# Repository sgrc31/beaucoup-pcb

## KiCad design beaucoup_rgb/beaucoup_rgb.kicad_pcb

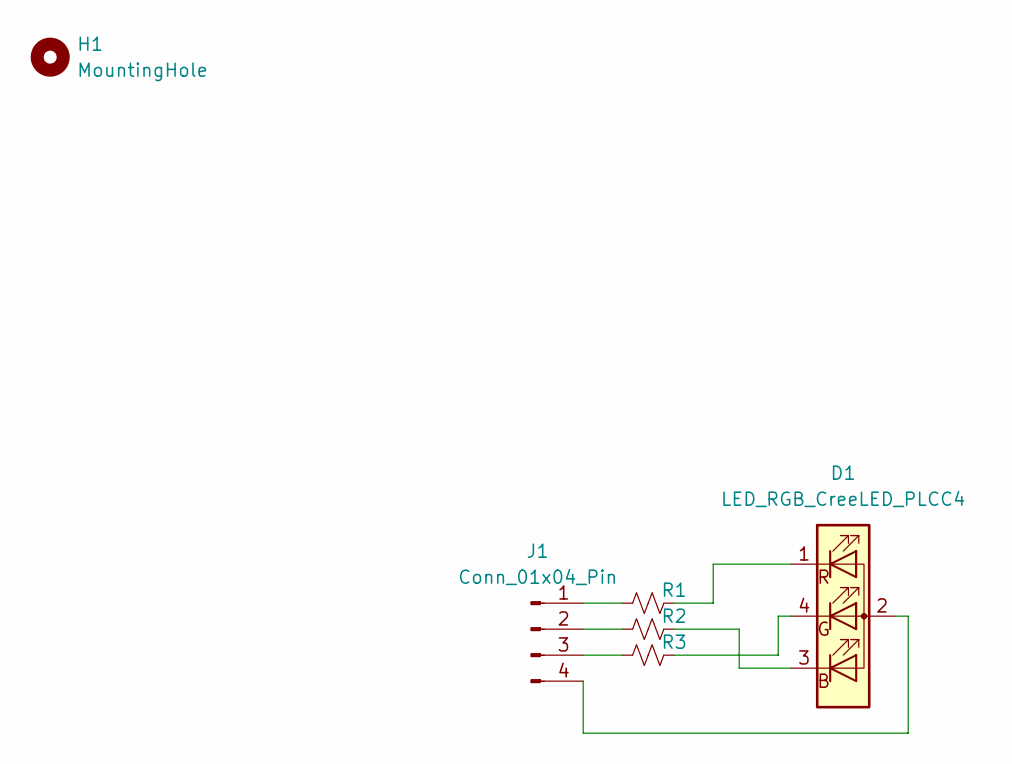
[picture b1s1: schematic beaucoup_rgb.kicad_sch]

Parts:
D1: LED_RGB_CreeLED_PLCC4; LED_RGB_CreeLED_CLV1A-FKB
H1: MountingHole; MountingHole_3.2mm_M3_ISO7380_Pad_TopOnly
J1: Conn_01x04_Pin; JST_XH_B4B-XH-A_1x04_P2.50mm_Vertical
R1, R2, R3: R_Small_US; R_1206_3216Metric_Pad1.30x1.75mm_HandSolder

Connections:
unnamed: D1.2 (A), J1.4
unnamed: D1.3 (BK), R2.1
unnamed: D1.4 (GK), R3.2
unnamed: D1.1 (RK), R1.2
unnamed: J1.1, R1.1
unnamed: J1.2, R2.2
unnamed: J1.3, R3.1

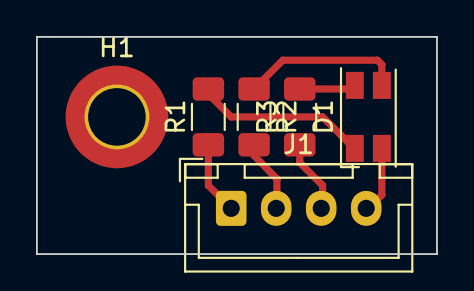
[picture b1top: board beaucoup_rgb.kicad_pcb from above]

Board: 2 copper layers, 22.2 x 12.1 mm, 6 parts (0 on the bottom side), 7 nets.

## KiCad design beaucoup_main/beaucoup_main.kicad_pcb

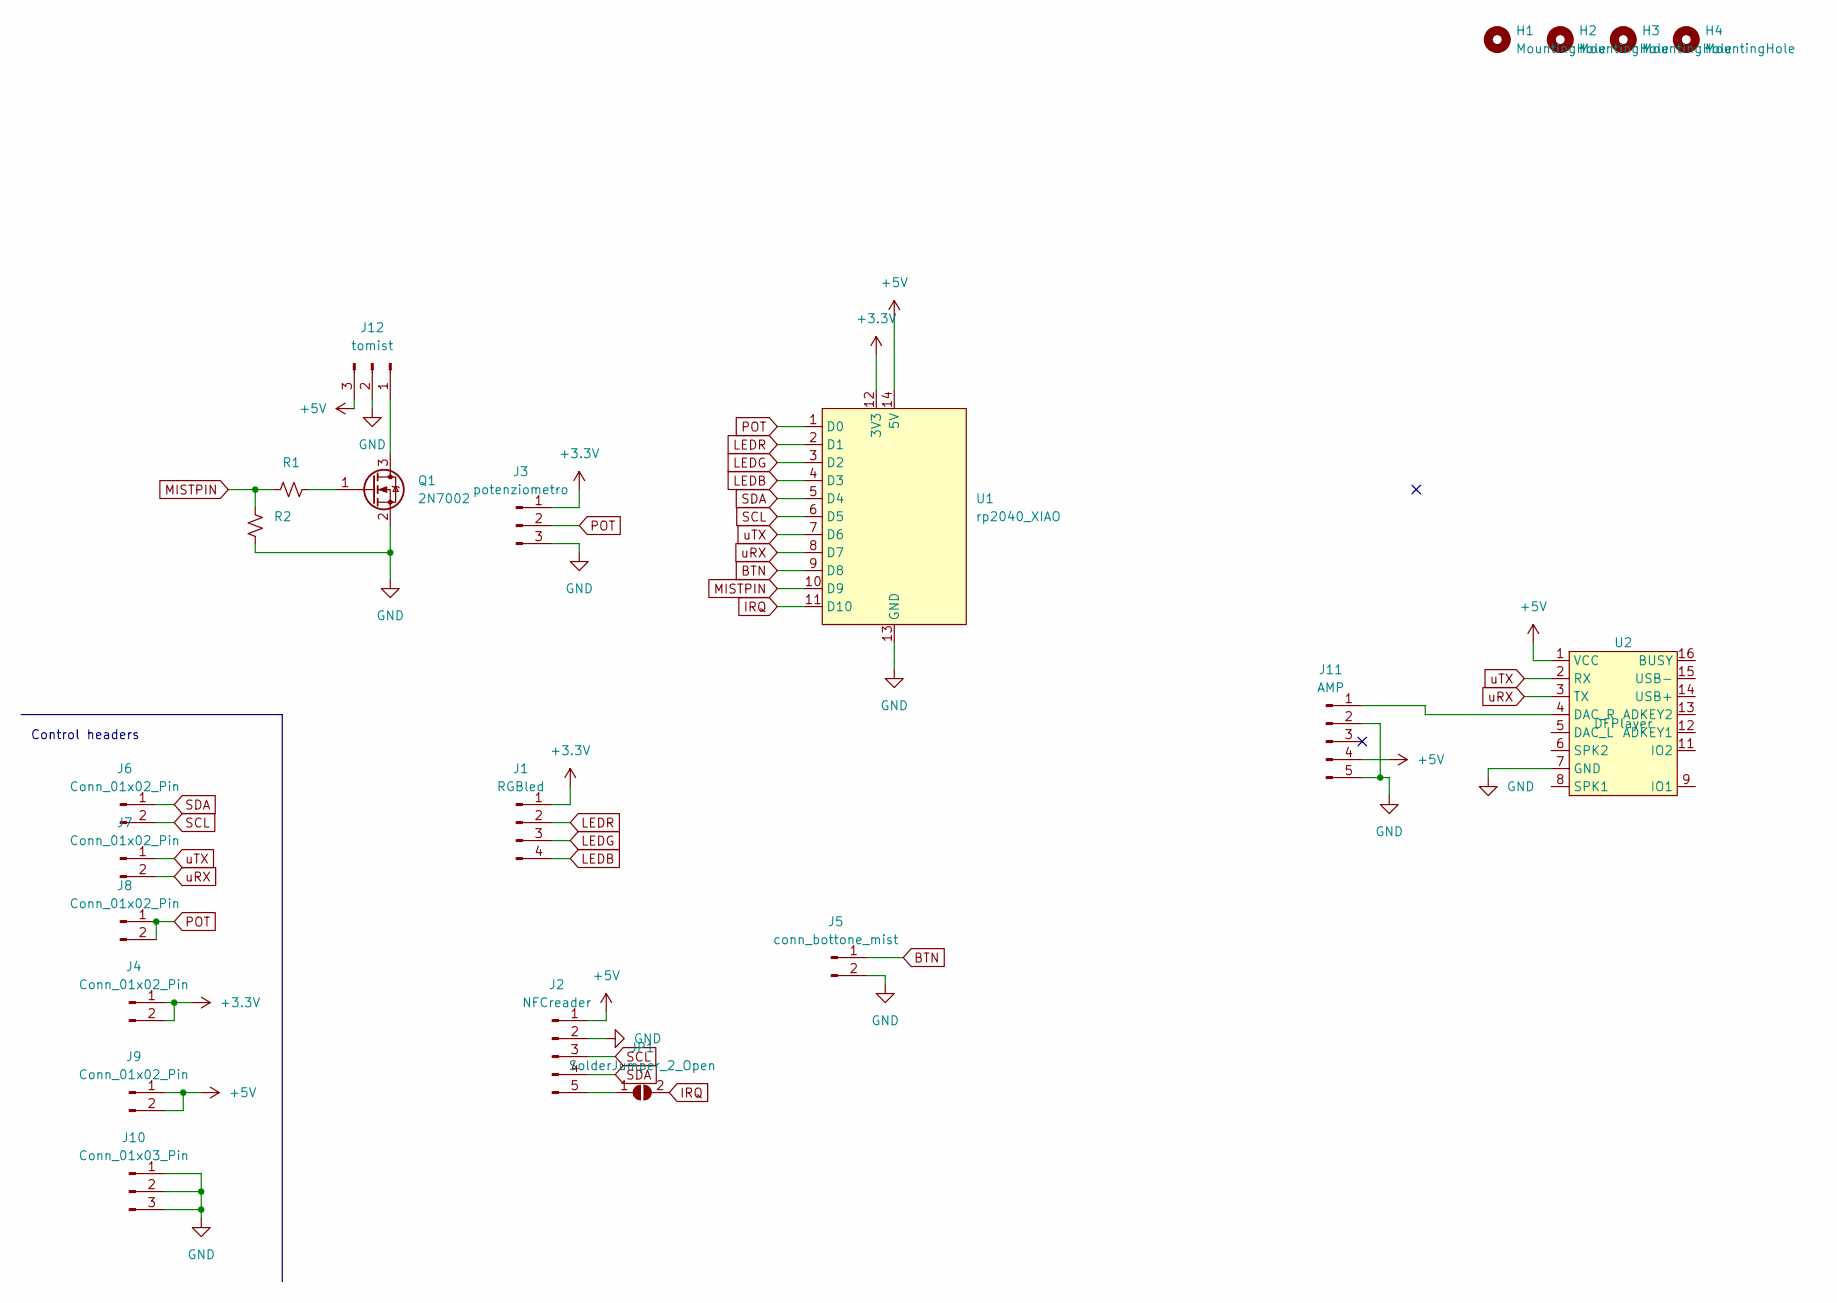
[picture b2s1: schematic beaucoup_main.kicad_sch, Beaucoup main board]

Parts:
H1, H2, H3, H4: MountingHole; MountingHole_3.2mm_M3_ISO7380_Pad
J1: RGBled; JST_XH_B4B-XH-A_1x04_P2.50mm_Vertical
J2: NFCreader; JST_XH_B5B-XH-A_1x05_P2.50mm_Vertical
J3: potenziometro; JST_XH_B3B-XH-A_1x03_P2.50mm_Vertical
J4, J6, J7, J8, J9: Conn_01x02_Pin; PinHeader_1x02_P2.54mm_Vertical
J5: conn_bottone_mist; JST_XH_B2B-XH-A_1x02_P2.50mm_Vertical
J10: Conn_01x03_Pin; PinHeader_1x03_P2.54mm_Vertical
J11: AMP; PinHeader_1x05_P2.54mm_Vertical
J12: tomist; JST_XH_B3B-XH-A_1x03_P2.50mm_Vertical
JP1: SolderJumper_2_Open; SolderJumper
Q1: 2N7002; SOT-23
R1, R2: R_Small_US; R_1206_3216Metric_Pad1.30x1.75mm_HandSolder
U1: rp2040_XIAO; XIAO_both
U2: DFPlayer

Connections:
+3.3V: J1.1, J3.1, J4.1, J4.2, U1.12 (3V3)
+5V: J2.1, J9.1, J9.2, J11.4, J12.3, U1.14 (5V), U2.1 (VCC)
BTN: J5.1, U1.9 (D8)
GND: J2.2, J3.3, J5.2, J10.1, J10.2, J10.3, J11.2, J11.5, J12.2, Q1.2 (S), R2.2, U1.13 (GND), U2.7 (GND), U2.10 (GND)
IRQ: JP1.2 (B), U1.11 (D10)
LEDB: J1.4, U1.4 (D3)
LEDG: J1.3, U1.3 (D2)
LEDR: J1.2, U1.2 (D1)
MISTPIN: R1.1, R2.1, U1.10 (D9)
unnamed: J2.5, JP1.1 (A)
unnamed: J11.1, U2.4 (DAC_R)
unnamed: J12.1, Q1.3 (D)
unnamed: Q1.1 (G), R1.2
POT: J3.2, J8.1, J8.2, U1.1 (D0)
SCL: J2.3, J6.2, U1.6 (D5)
SDA: J2.4, J6.1, U1.5 (D4)
uRX: J7.2, U1.8 (D7), U2.3 (TX)
uTX: J7.1, U1.7 (D6), U2.2 (RX)

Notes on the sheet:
Control headers

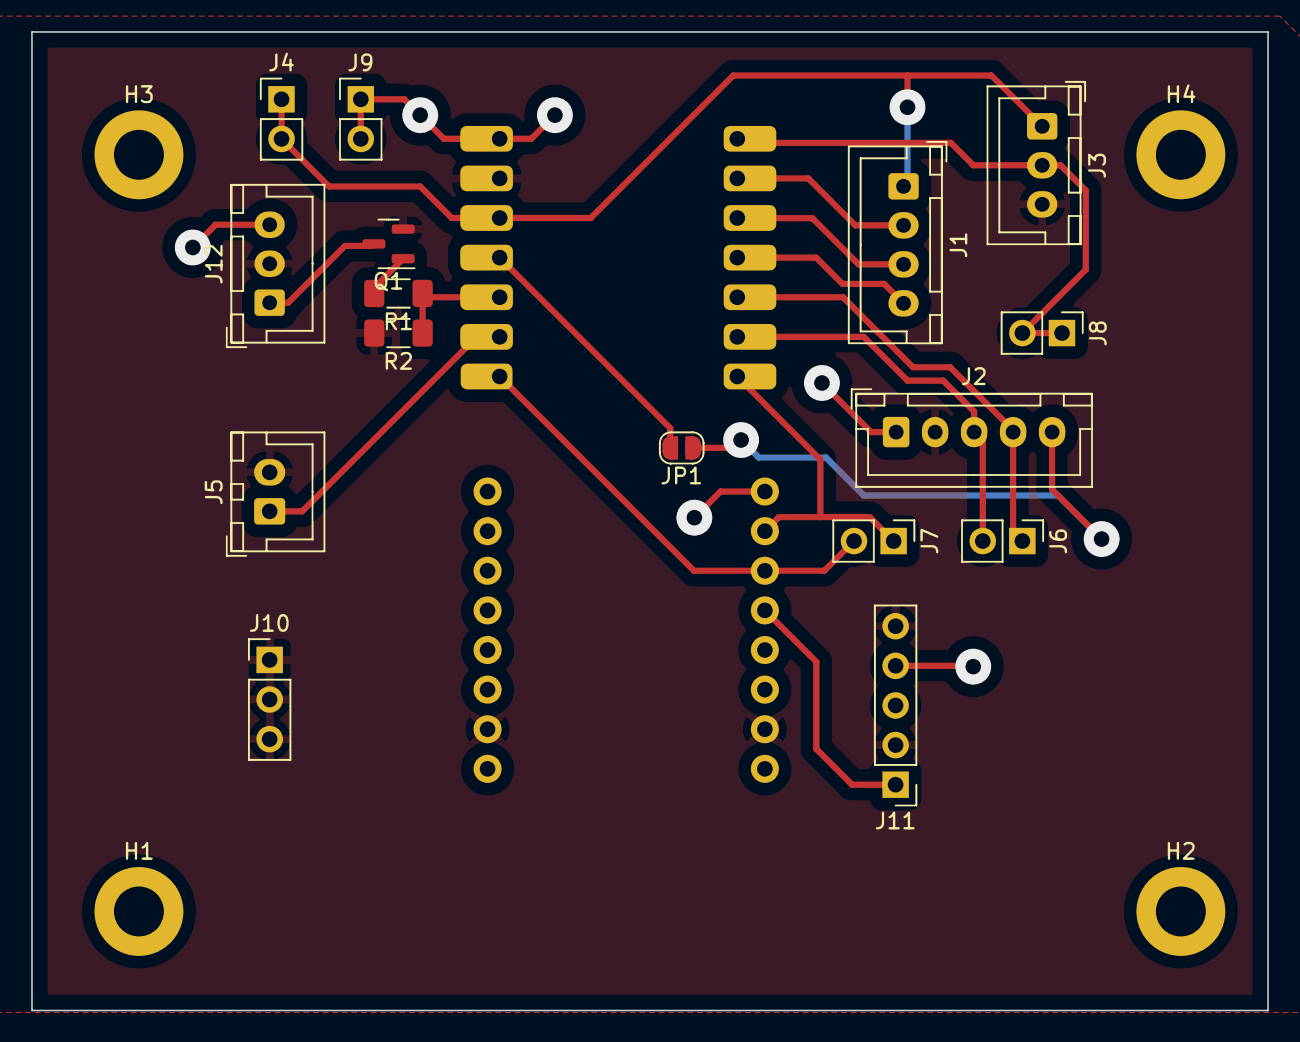
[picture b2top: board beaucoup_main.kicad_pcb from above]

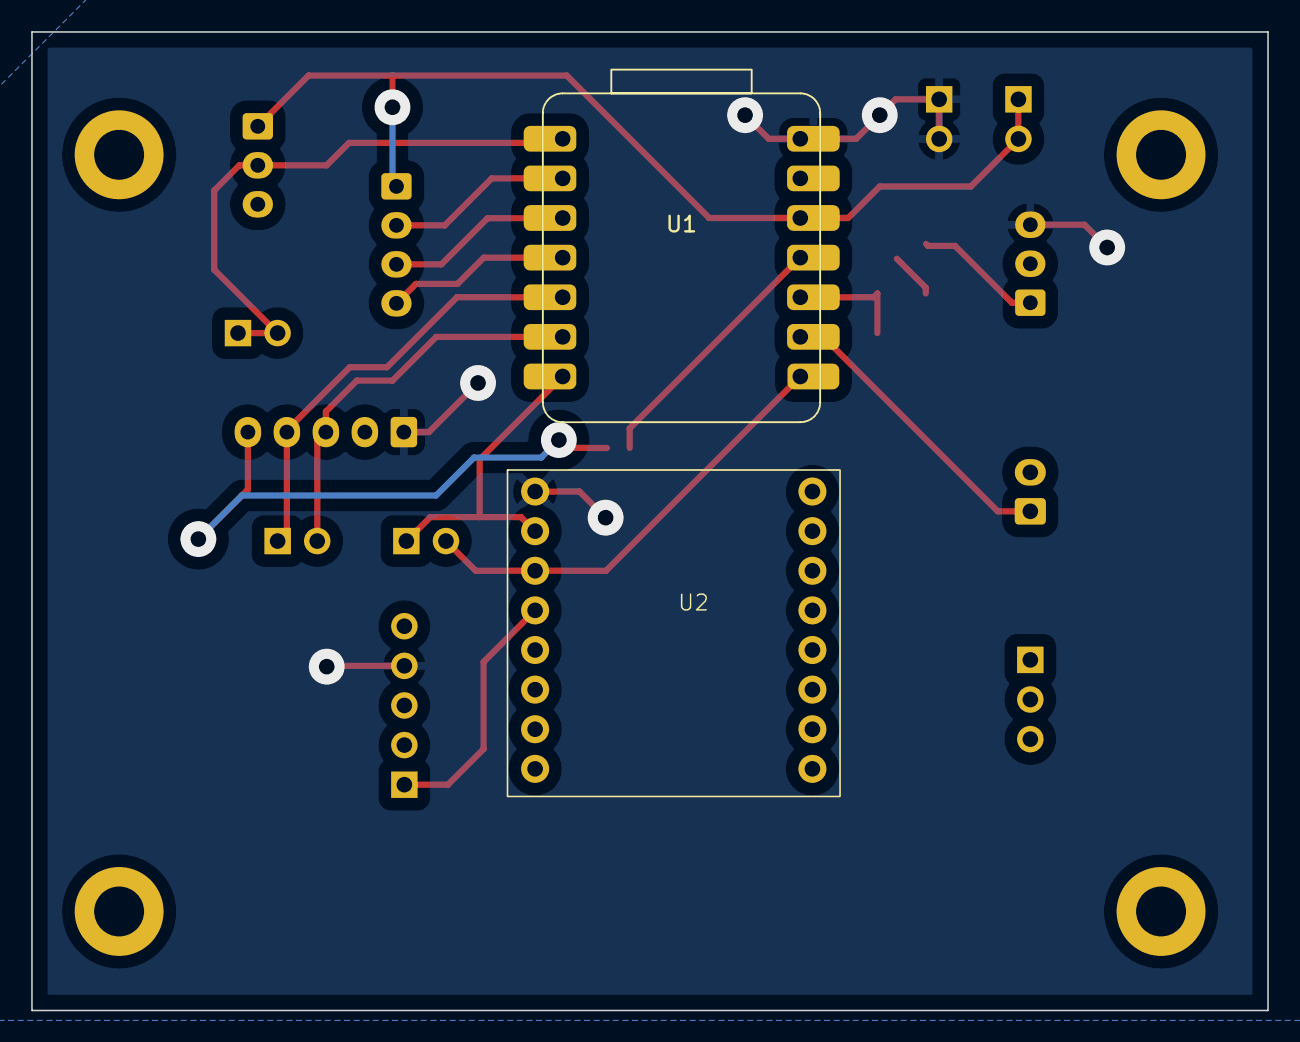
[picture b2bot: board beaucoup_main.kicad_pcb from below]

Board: 4 copper layers, 79.2 x 62.7 mm, 22 parts (2 on the bottom side), 18 nets.

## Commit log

2023-07-18 add rgb led board
2023-07-20 Main pcb should be ready for production
2023-07-25 File lavorazione revA
2023-07-25 Aggiunge file lavorazione rgb revA
